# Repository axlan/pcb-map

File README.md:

# PCB Map Display

This project is two related parts. First is the PCB map itself manufactured by [PCBWay](https://www.pcbway.com/). This is a PCB art piece that combines a map of the East Bay of California with an LED matrix display. The second part is the software to control the display.

The software is designed to be a fairly flexible controller for a matrix display, and the whole project could easily be used with a map printed on paper instead of a custom PCB.

<!-- <video src="docs/demo.mp4" autoplay loop muted playsinline></video> -->
<video src="https://github.com/user-attachments/assets/1058f474-8182-4159-85aa-21de5fce3b74" autoplay loop muted playsinline></video>

See <https://www.robopenguins.com/pcb-map/> for the design process.

---

## PCB Design Files

The design files can be found in `design/`.

The full design is in `design/map_board.kicad_pcb`, while the schematic for the ESP32 connected the the LED panel was designed in `design/wiring_project/map_lights.kicad_pro`

I came up with this project in response to an offer from [PCBWay](https://www.pcbway.com/) to manufacture a board for free in exchange for writing about the experience. The process of submitting the design files was straightforward, and I especially appreciated that their preview system showed the selected solder mask and surface finish colors. The design was flagged for manual review, and I had to confirm that the strange mostly-artistic board layout was intentional. This was entirely reasonable for a PCB that was deliberately designed to be mostly non-functional.

---

## Firmware

The firmware is located in the `firmware/` directory and is built using PlatformIO.

### Supported Matrix Display

The matrix display that this project was tested with is the:
[Waveshare RGB Full-Color LED Matrix Panel, 5mm Pitch, 64×32 Pixels](https://www.amazon.com/dp/B0CLV5MHPX)

It worked with the `ESP32 HUB75 LED MATRIX PANEL DMA Display` library out of the box, only needing to modify the `mxconfig.clkphase = false`.

My display was labeled as `P5(2121)-3264-16S-M5` (32x64 1/16 scan) and used the `RUC7258D`, `SM16208SJ`, and `MW245BC` control chips.

### Building and Uploading
To upload the firmware to your ESP32, use the provided helper script:
```bash
./scripts/upload_firmware.sh
```
This script uses PlatformIO to build the project and upload it to `pcb-map.local` (once the device is on your network).

### Initial WiFi Setup
If the device has no saved WiFi credentials, it will start an Access Point named **pcb-map-ap**. Connect to this AP with your phone or computer to configure your local WiFi settings via the captive portal.

### OTA Updates
The firmware supports Over-The-Air updates. Once configured on your network, you can re-flash the device wirelessly using PlatformIO's OTA functionality.

---

## Simulator

The simulator allows you to run the pcb-map logic on your desktop. It renders the LED matrix using SFML and connects to an MQTT broker to receive commands exactly like the hardware would.

### Building the Simulator
The simulator requires SFML, Paho MQTT C++, and OpenSSL. It uses CMake for building:

```bash
cd firmware/simulation
mkdir build && cd build
cmake ..
make
./matrix_sim
```
By default, it attempts to connect to a local MQTT broker at `tcp://localhost:1883`.

---

## Python Tools

The project includes a suite of Python scripts located in the `python/` directory to manage the device and feed it data.

### Environment Setup
Use uv to manage the Python environment:
```bash
uv --directory=python sync
source python/.venv/bin/activate
```

Install shell tab completion for the commands:
```bash
control-server --install-completion 
device-setup --install-completion 
```

### Configuration
Set up your environment variables (usually via a script like `pcb_map_args.sh`):
```bash
export MQTT_HOSTNAME="your-broker-address"
export MQTT_USE_TLS=1
export MQTT_USERNAME="user"
export MQTT_PASSWORD="pass"
# Used to query the Google Maps API for route information
export GOOGLE_MAPS_API_KEY="your-api-key"
# Used to set specific colors for people when using shared location display
export USER_COLORS_FILE="$HOME/user_colors.json"
```

#### user_colors.json
Define specific colors for people when using shared location display. When specified, only people in this configuration will be displayed.:
```json
{
    "me": [0, 255, 0],
    "Joe Smith": [0, 0, 255],
    "Mary Sue": [255, 0, 0]
}
```

### Key Commands

#### Device Setup (`device-setup`)
- `find-devices`: Discovers the board via mDNS, MQTT, or by scanning for the setup AP.
- `setup-mqtt`: Configures the MQTT broker credentials on the device via a local UDP broadcast.
- `clear-wifi-creds`: Resets the WiFi settings on the hardware.

Here's a rundown of how device configuration works:

The `find-devices` command gives the context for what state the device is in.

#### Control Server (`control-server`)
- `display-shared-locations`: Fetches shared Google locations and plots them on the matrix.
- `set-background-image [path]`: Uploads and displays a 64x32 RGB image as the map background.
- `simulate-route --start "Home" --dest "Work"`: Calculates a route and animates it on the display.
- `set-brightness [0-100]`: Adjusts the LED intensity.
- `clear-display`: Clears all active sprites and hides the background.
- `lat-long-to-xy`: A utility to check where a coordinate falls on the matrix grid.

---

## Development Utilities

**Formatting Code** (C++):
```bash
clang-format -style=Google -i firmware/src/*
```

## TODO
 - Improve fetching Google map creds for location sharing from a remote browser
 - Make location share able to run as a server more robustly
 - Scrape Google calendar for events with locations for drawing routes
 - Separate MQTT client and config into reusable library
 - Add MQTT errors stat

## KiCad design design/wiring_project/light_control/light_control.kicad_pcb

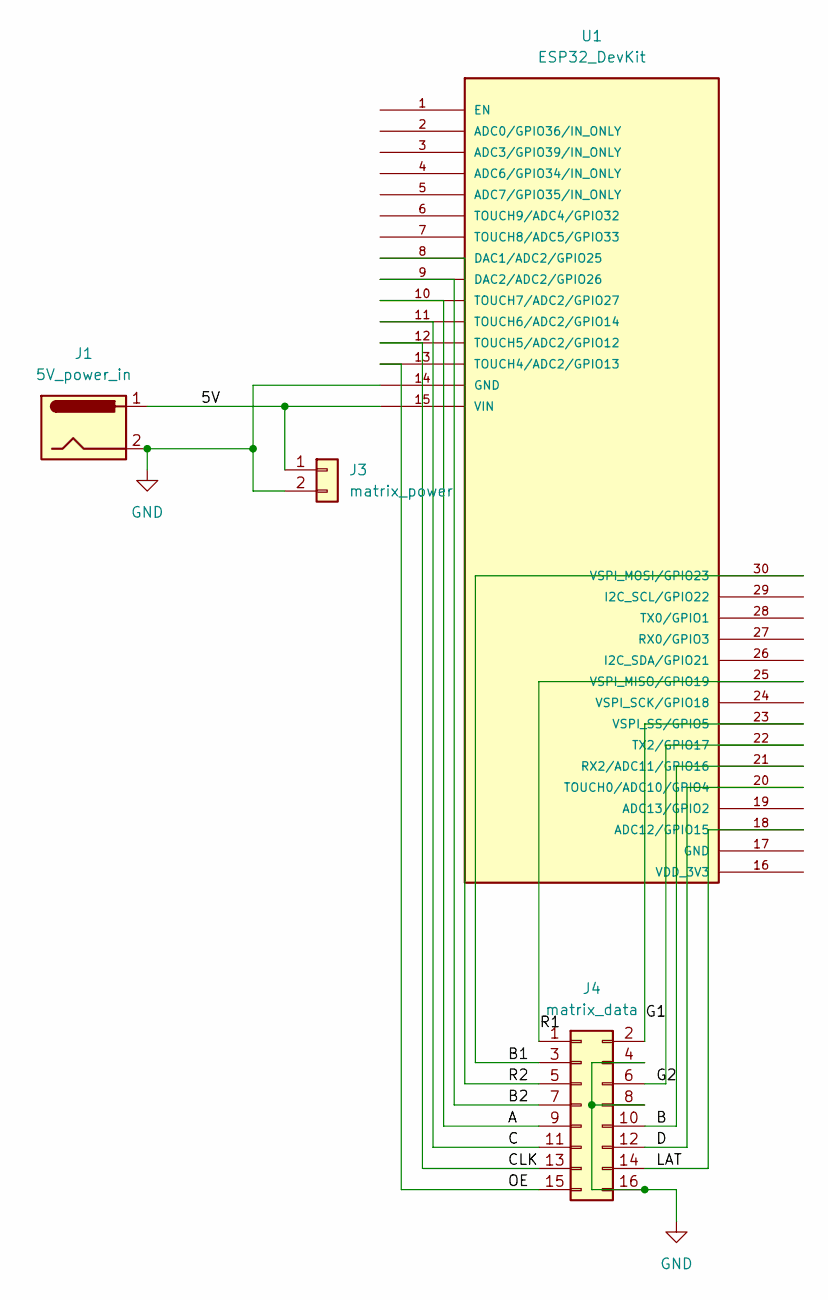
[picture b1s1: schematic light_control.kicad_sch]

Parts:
J1: 5V_power_in; BarrelJack_Horizontal
J3: matrix_power; PinHeader_1x02_P2.54mm_Vertical
J4: matrix_data; PinHeader_2x08_P2.54mm_Vertical
U1: ESP32_DevKit; esp32_devkit

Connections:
/5V: J1.1, J3.1, U1.15 (VIN)
/A: J4.9, U1.10 (TOUCH7/ADC2/GPIO27)
/B: J4.10, U1.21 (RX2/ADC11/GPIO16)
/B1: J4.3, U1.30 (VSPI_MOSI/GPIO23)
/B2: J4.7, U1.9 (DAC2/ADC2/GPIO26)
/C: J4.11, U1.11 (TOUCH6/ADC2/GPIO14)
/CLK: J4.13, U1.12 (TOUCH5/ADC2/GPIO12)
/D: J4.12, U1.20 (TOUCH0/ADC10/GPIO4)
/G1: J4.2, U1.23 (VSPI_SS/GPIO5)
/G2: J4.6, U1.22 (TX2/GPIO17)
/LAT: J4.14, U1.18 (ADC12/GPIO15)
/OE: J4.15, U1.13 (TOUCH4/ADC2/GPIO13)
/R1: J4.1, U1.25 (VSPI_MISO/GPIO19)
/R2: J4.5, U1.8 (DAC1/ADC2/GPIO25)
GND: J1.2, J3.2, J4.4, J4.8, J4.16, U1.14 (GND)

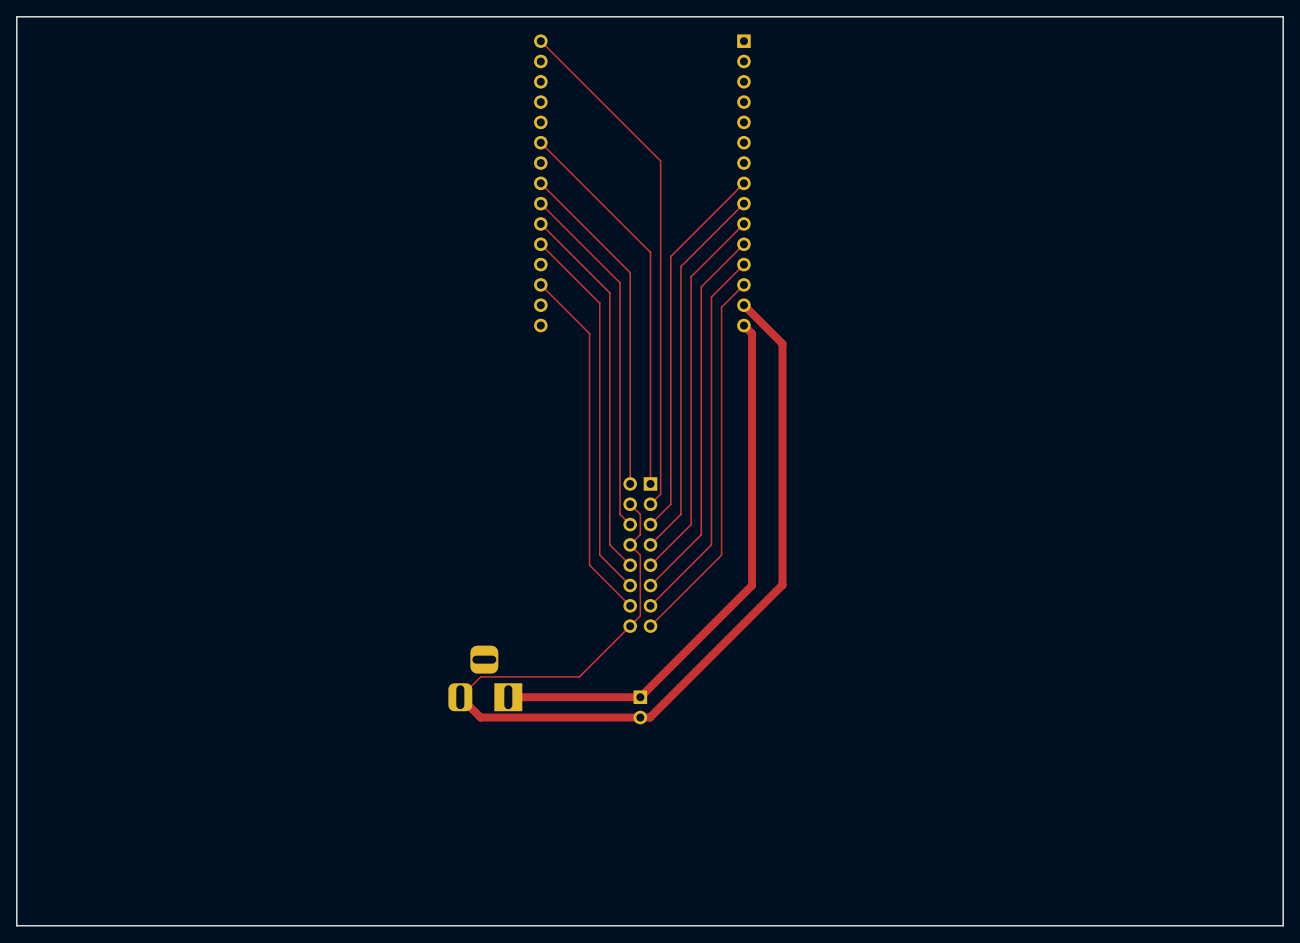
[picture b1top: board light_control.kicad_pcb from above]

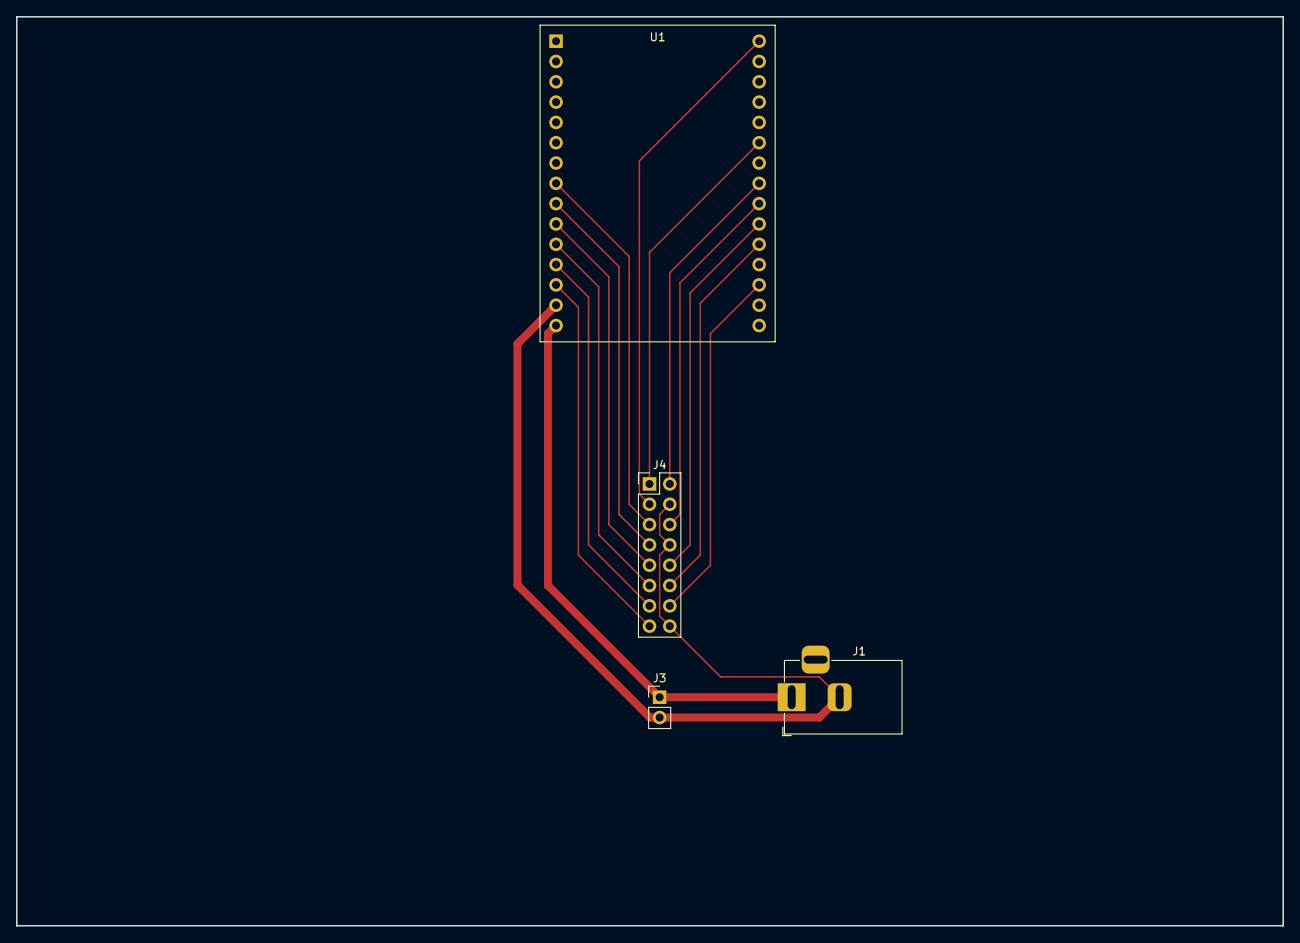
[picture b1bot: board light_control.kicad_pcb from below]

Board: 2 copper layers, 158.4 x 113.7 mm, 4 parts (4 on the bottom side), 15 nets.

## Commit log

2026-04-25 Tested MQTT config.
2026-04-28 Implement MVP with simulator.
2026-04-29 Cleanup setup tool
2026-04-30 Make Python tool a module.
2026-05-04 Basic tests working in sim.
2026-05-04 Attempt to draw background less.
2026-05-05 Get route simulation working.
2026-05-05 Add route fade.
2026-05-05 Basic location server working.
2026-05-05 Add color map feature, and clear display command.
2026-05-05 Make setting background image more flexible.
2026-05-05 Python formatting.
2026-05-05 C++ formatting.
2026-05-06 Add set brightness
2026-05-06 Add LED pulse option, and some cleanup.
2026-05-06 Switch to using google maps for routing.
2026-05-07 Add command to clear WiFi
2026-05-07 Get simulation with integrated routes working.
2026-05-07 Get demo working on HW.
2026-05-12 Update README.
2026-05-12 Fix video in README.md
2026-05-12 Document the provisioning process.
2026-05-13 Added details of display.
2026-05-14 Fix setting and saving brightness.
2026-05-14 Add MQTT parameters to WifiManager.
2026-05-14 Remove outdated comment.
2026-05-16 Changes to make server.
2026-05-16 Fix path.
2026-05-16 Add hostname
